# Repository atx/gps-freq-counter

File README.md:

# gps-freq-counter
Frequency counter using a GPS receiver PPS output as its reference

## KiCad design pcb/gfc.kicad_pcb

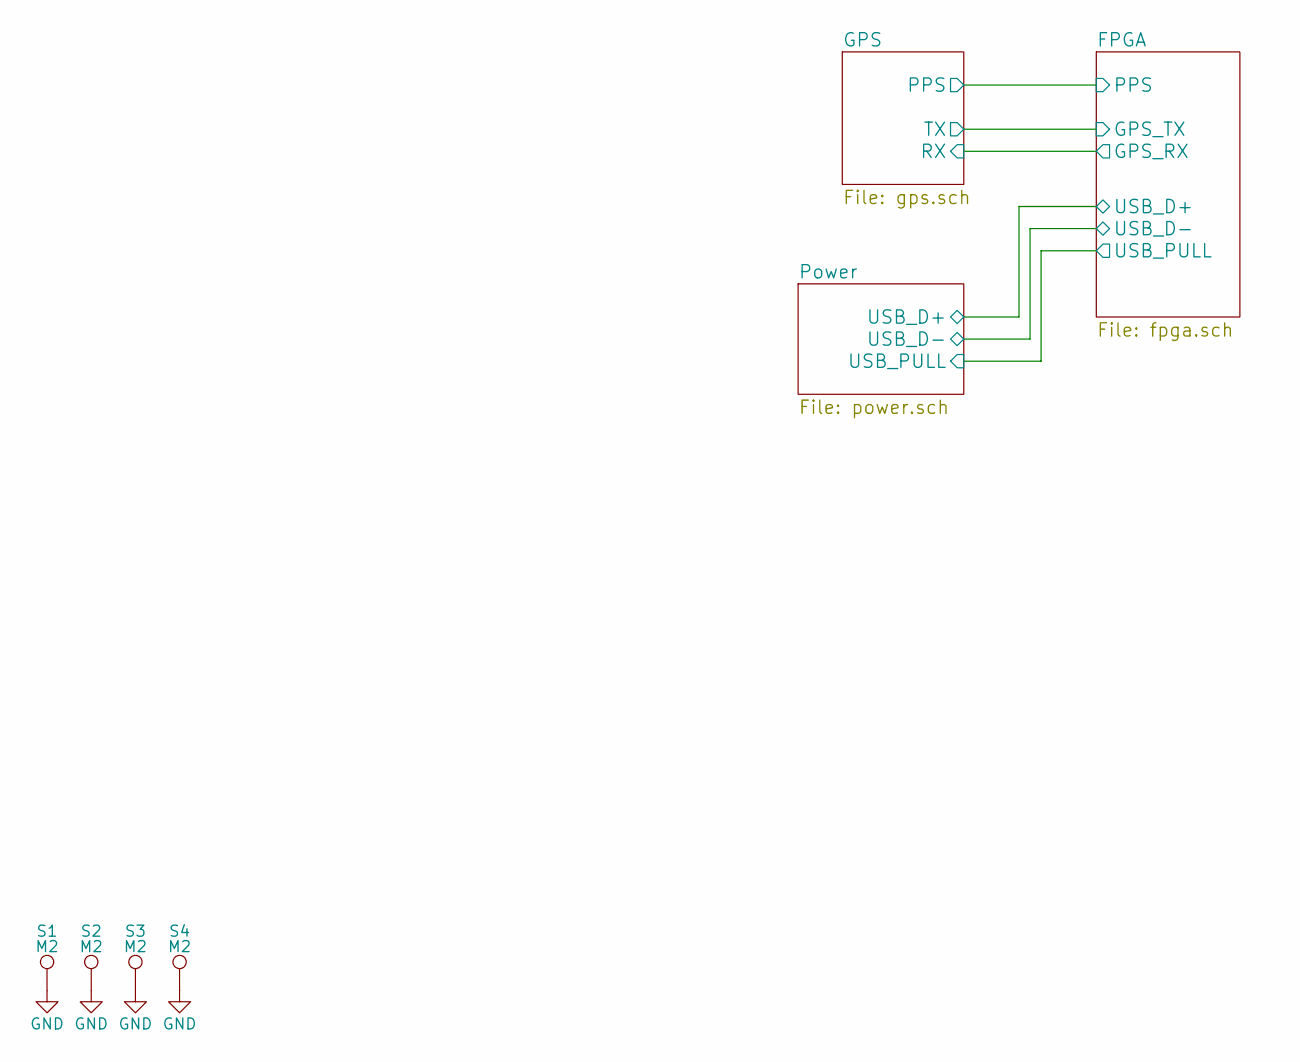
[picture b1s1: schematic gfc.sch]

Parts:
S1, S2, S3, S4: M2; MountingHole_2.2mm_M2_Pad

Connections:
GND: S1.1, S2.1, S3.1, S4.1; also elsewhere on the board

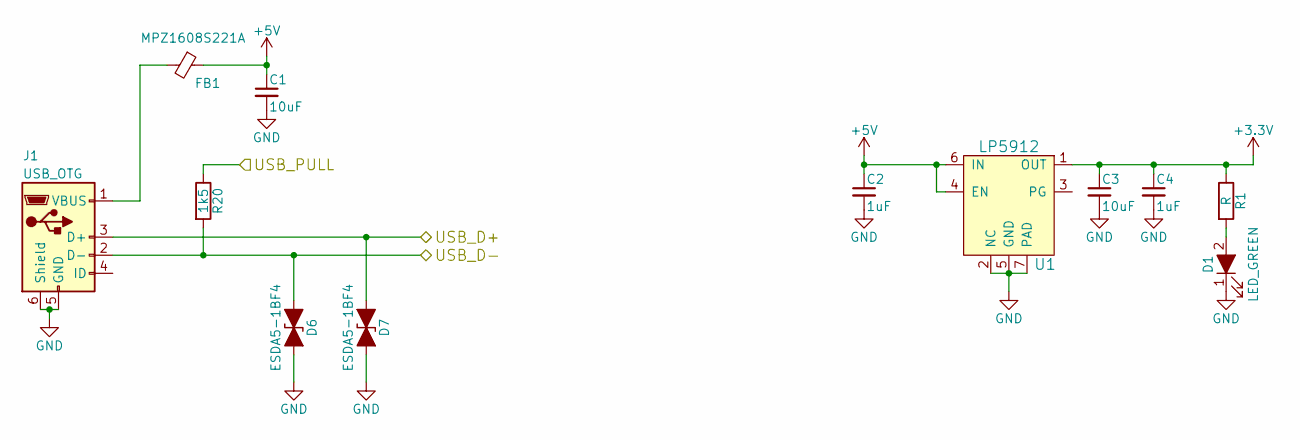
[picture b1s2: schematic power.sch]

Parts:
C1, C3: 10uF; C_0603
C2, C4: 1uF; C_0402
D1: LED_GREEN; LED_0603
D6, D7: ESDA5-1BF4; D_0603
FB1: MPZ1608S221A; L_0603
J1: USB_OTG; USB_Micro-B
R1: R; R_0402
R20: 1k5; R_0402
U1: LP5912; WSON-6-DRV

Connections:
+3V3: C3.1, C4.1, R1.1, U1.1 (OUT); also elsewhere on the board
+5V: C1.1, C2.1, FB1.1, U1.4 (EN), U1.6 (IN)
/FPGA/USB_D+: D7.1 (A1), J1.3 (D+); also elsewhere on the board
/FPGA/USB_D-: D6.1 (A1), J1.2 (D-), R20.2; also elsewhere on the board
/FPGA/USB_PULL: R20.1; also elsewhere on the board
GND: C1.2, C2.2, C3.2, C4.2, D1.1 (K), D6.2 (A2), D7.2 (A2), J1.5 (GND), J1.6 (Shield), U1.2 (NC), U1.5 (GND), U1.7 (PAD); also elsewhere on the board
unnamed: D1.2 (A), R1.2
unnamed: FB1.2, J1.1 (VBUS)

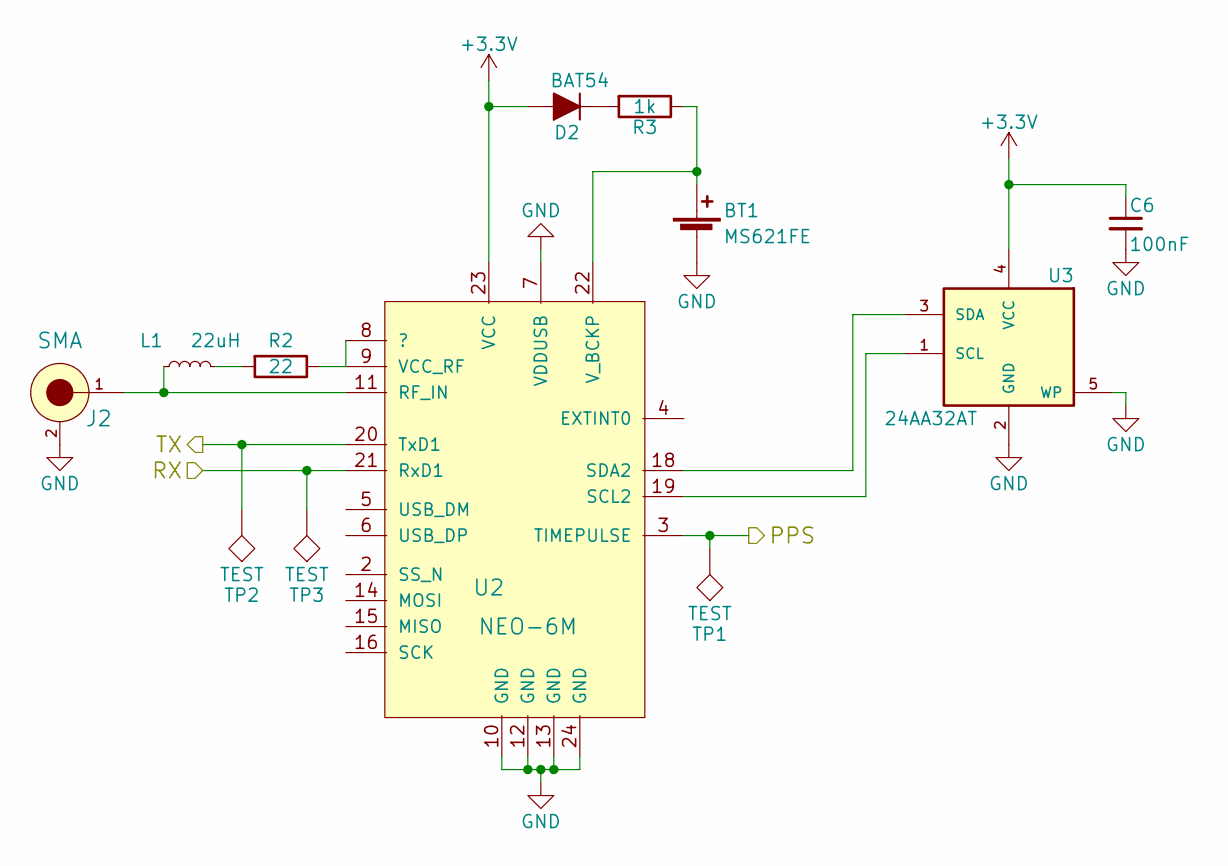
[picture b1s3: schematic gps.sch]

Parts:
BT1: MS621FE
C6: 100nF; C_0402
D2: BAT54; D_SOT-23_ANK
J2: SMA; CON-SMA-EDGE
L1: 22uH; L_0805
R2: 22; R_0402
R3: 1k; R_0402
TP1, TP2, TP3: TEST; PINTST
U2: NEO-6M; NEO-6
U3: 24AA32AT; SOT-23-5

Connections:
+3V3: C6.1, D2.2 (A), U2.23 (VCC), U3.4 (VCC); also elsewhere on the board
/FPGA/GPS_RX: TP3.1, U2.21 (RxD1); also elsewhere on the board
/FPGA/GPS_TX: TP2.1, U2.20 (TxD1); also elsewhere on the board
/FPGA/PPS: TP1.1, U2.3 (TIMEPULSE); also elsewhere on the board
GND: BT1.2 (-), C6.2, J2.2, J2.3, J2.4, J2.5, U2.7 (VDDUSB), U2.10 (GND), U2.12 (GND), U2.13 (GND), U2.24 (GND), U3.2 (GND), U3.5 (WP); also elsewhere on the board
unnamed: BT1.1 (+), R3.1, U2.22 (V_BCKP)
unnamed: D2.1 (K), R3.2
unnamed: J2.1, L1.1, U2.11 (RF_IN)
unnamed: L1.2, R2.2
unnamed: R2.1, U2.8 (?), U2.9 (VCC_RF)
unnamed: U2.18 (SDA2), U3.3 (SDA)
unnamed: U2.19 (SCL2), U3.1 (SCL)

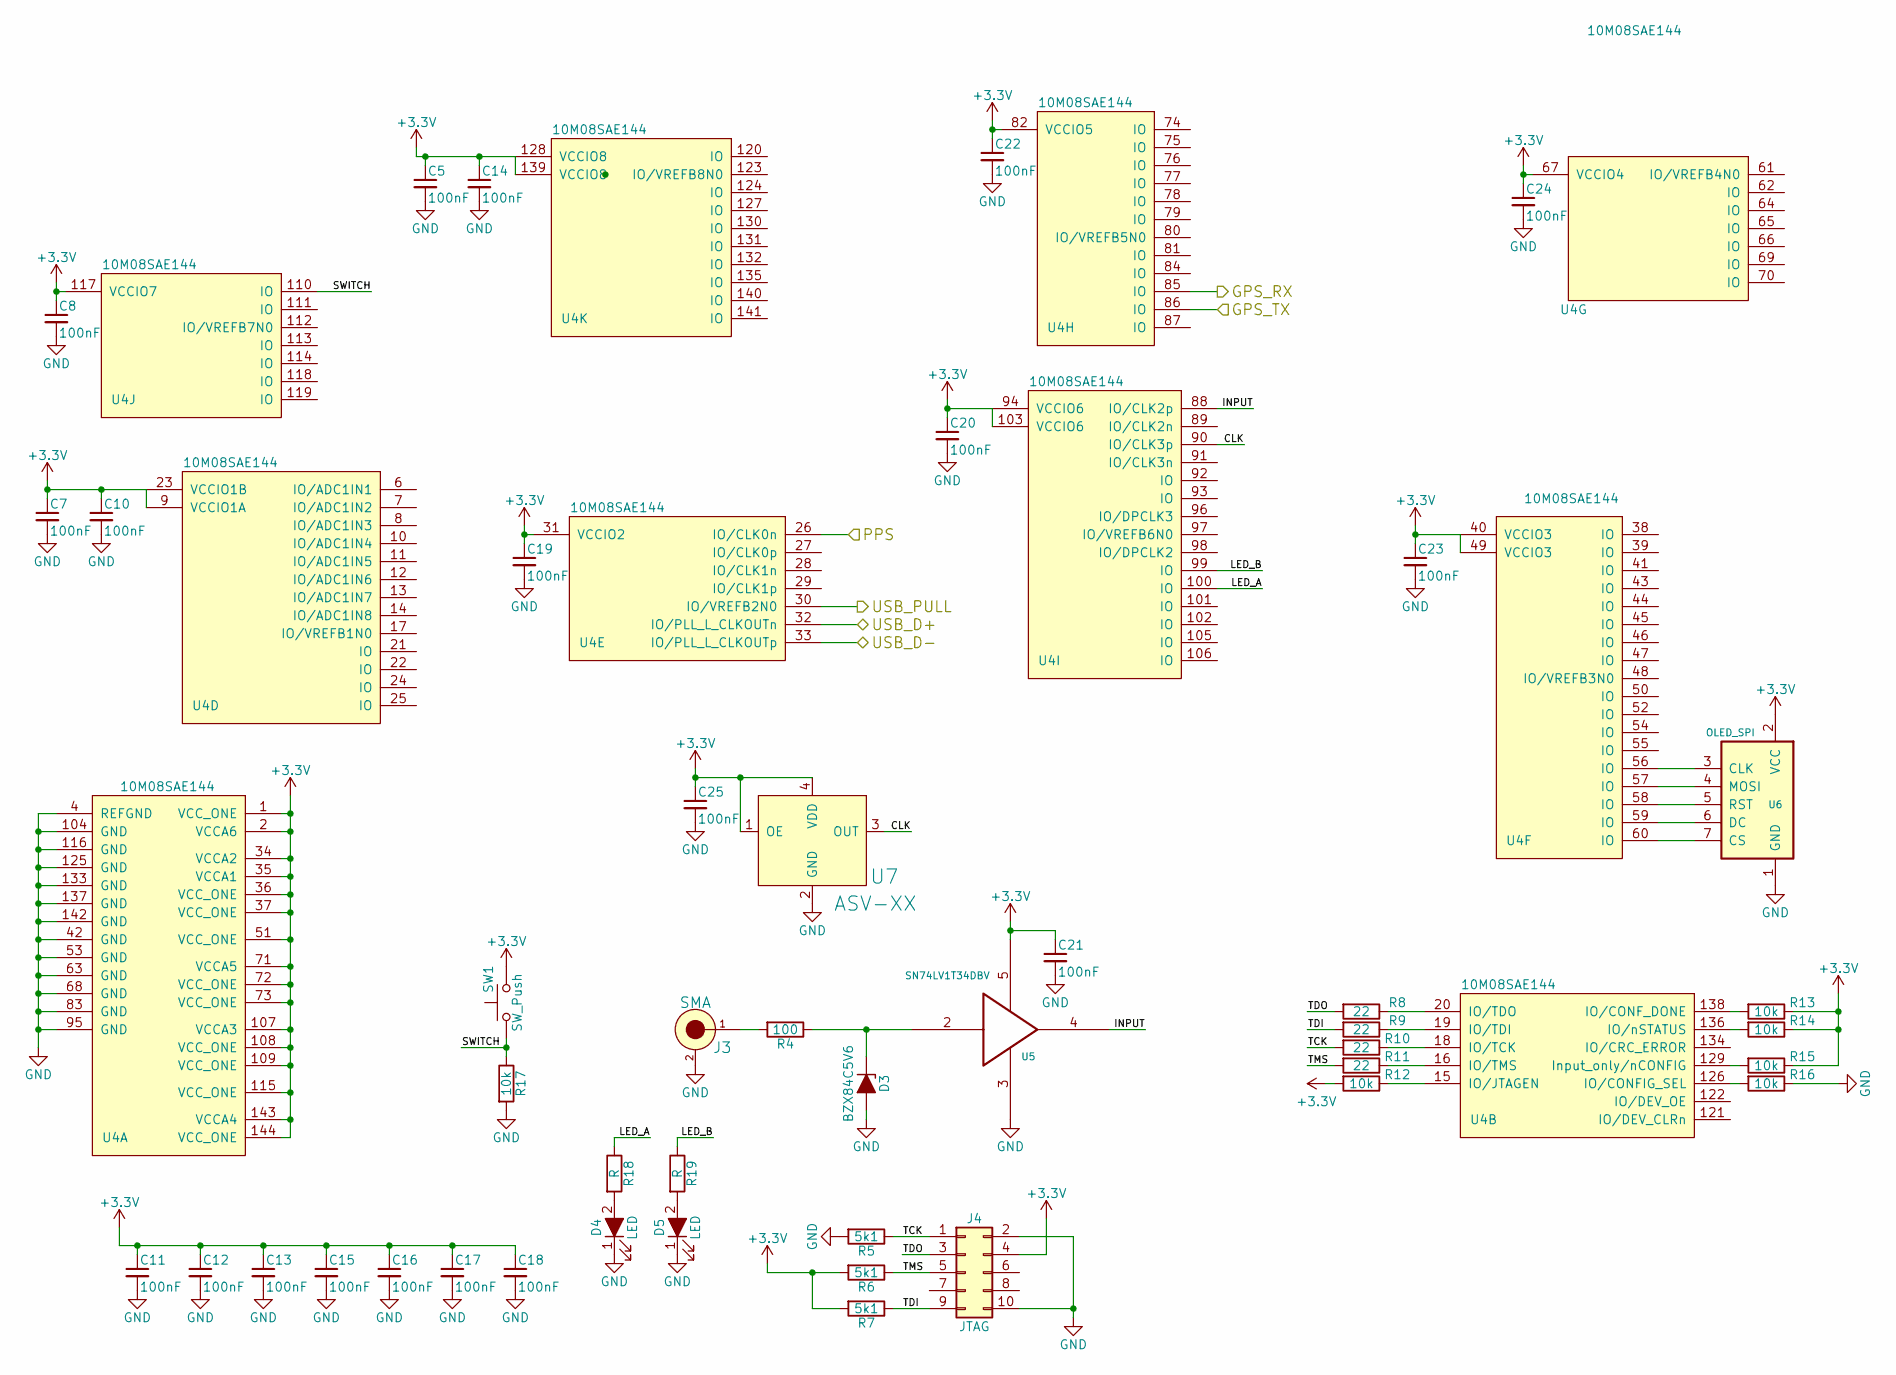
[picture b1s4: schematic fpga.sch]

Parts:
C5, C7, C8, C10, C11, C12, C13, C14, C15, C16, C17, C18, C19, C20, C21, C22, C23, C24, C25: 100nF; C_0402
D3: BZX84C5V6; D_SOT-23_ANK
D4, D5: LED; LED_0603
J3: SMA; CON-SMA-EDGE
J4: JTAG; Pin_Header_Straight_2x05_Pitch2.54mm_SMD
R4: 100; R_0402
R5, R6, R7: 5k1; R_0402
R8, R9, R10, R11: 22; R_0402
R12, R13, R14, R15, R16, R17: 10k; R_0402
R18, R19: R; R_0402
SW1: SW_Push; SW_PUSH_6mm_h13mm
U4: 10M08SAE144; TQFP-144_20x20mm_Pitch0.5mm
U5: SN74LV1T34DBV; SOT-23-5
U6: OLED_SPI
U7: ASV-XX

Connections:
+3V3: C5.1, C7.1, C8.1, C10.1, C11.1, C12.1, C13.1, C14.1, C15.1, C16.1, C17.1, C18.1, C19.1, C20.1, C21.1, C22.1, C23.1, C24.1, C25.1, J4.4, R6.2, R7.2, R12.2, R13.1, R14.1, R15.1, SW1.2, U4.1 (VCC_ONE), U4.2 (VCCA6), U4.9 (VCCIO1A), U4.23 (VCCIO1B), U4.31 (VCCIO2), U4.34 (VCCA2), U4.35 (VCCA1), U4.36 (VCC_ONE), U4.37 (VCC_ONE), U4.40 (VCCIO3), U4.49 (VCCIO3), U4.51 (VCC_ONE), U4.67 (VCCIO4), U4.71 (VCCA5), U4.72 (VCC_ONE), U4.73 (VCC_ONE), U4.82 (VCCIO5), U4.94 (VCCIO6), U4.103 (VCCIO6), U4.107 (VCCA3), U4.108 (VCC_ONE), U4.109 (VCC_ONE), U4.115 (VCC_ONE), U4.117 (VCCIO7), U4.128 (VCCIO8), U4.139 (VCCIO8), U4.143 (VCCA4), U4.144 (VCC_ONE), U5.5, U6.2 (VCC), U7.1 (OE), U7.4 (VDD); also elsewhere on the board
/FPGA/CLK: U4.90 (IO/CLK3p), U7.3 (OUT)
/FPGA/GPS_RX: U4.85 (IO); also elsewhere on the board
/FPGA/GPS_TX: U4.86 (IO); also elsewhere on the board
/FPGA/INPUT: U4.88 (IO/CLK2p), U5.4
/FPGA/LED_A: R18.1, U4.100 (IO)
/FPGA/LED_B: R19.1, U4.99 (IO)
/FPGA/PPS: U4.26 (IO/CLK0n); also elsewhere on the board
/FPGA/SWITCH: R17.1, SW1.1, U4.110 (IO)
/FPGA/TCK: J4.1, R5.1, R10.2
/FPGA/TDI: J4.9, R7.1, R9.2
/FPGA/TDO: J4.3, R8.2
/FPGA/TMS: J4.5, R6.1, R11.2
/FPGA/USB_D+: U4.32 (IO/PLL_L_CLKOUTn); also elsewhere on the board
/FPGA/USB_D-: U4.33 (IO/PLL_L_CLKOUTp); also elsewhere on the board
/FPGA/USB_PULL: U4.30 (IO/VREFB2N0); also elsewhere on the board
GND: C5.2, C7.2, C8.2, C10.2, C11.2, C12.2, C13.2, C14.2, C15.2, C16.2, C17.2, C18.2, C19.2, C20.2, C21.2, C22.2, C23.2, C24.2, C25.2, D3.2 (A), D4.1 (K), D5.1 (K), J3.2, J3.3, J3.4, J3.5, J4.2, J4.10, R5.2, R16.1, R17.2, U4.4 (REFGND), U4.42 (GND), U4.53 (GND), U4.63 (GND), U4.68 (GND), U4.83 (GND), U4.95 (GND), U4.104 (GND), U4.116 (GND), U4.125 (GND), U4.133 (GND), U4.137 (GND), U4.142 (GND), U5.3, U6.1 (GND), U7.2 (GND); also elsewhere on the board
unnamed: D3.1 (K), R4.1, U5.2
unnamed: D4.2 (A), R18.2
unnamed: D5.2 (A), R19.2
unnamed: J3.1, R4.2
unnamed: R8.1, U4.20 (IO/TDO)
unnamed: R9.1, U4.19 (IO/TDI)
unnamed: R10.1, U4.18 (IO/TCK)
unnamed: R11.1, U4.16 (IO/TMS)
unnamed: R12.1, U4.15 (IO/JTAGEN)
unnamed: R13.2, U4.138 (IO/CONF_DONE)
unnamed: R14.2, U4.136 (IO/nSTATUS)
unnamed: R15.2, U4.129 (Input_only/nCONFIG)
unnamed: R16.2, U4.126 (IO/CONFIG_SEL)
unnamed: U4.56 (IO), U6.3 (CLK)
unnamed: U4.57 (IO), U6.4 (MOSI)
unnamed: U4.58 (IO), U6.5 (RST)
unnamed: U4.59 (IO), U6.6 (DC)
unnamed: U4.60 (IO), U6.7 (CS)

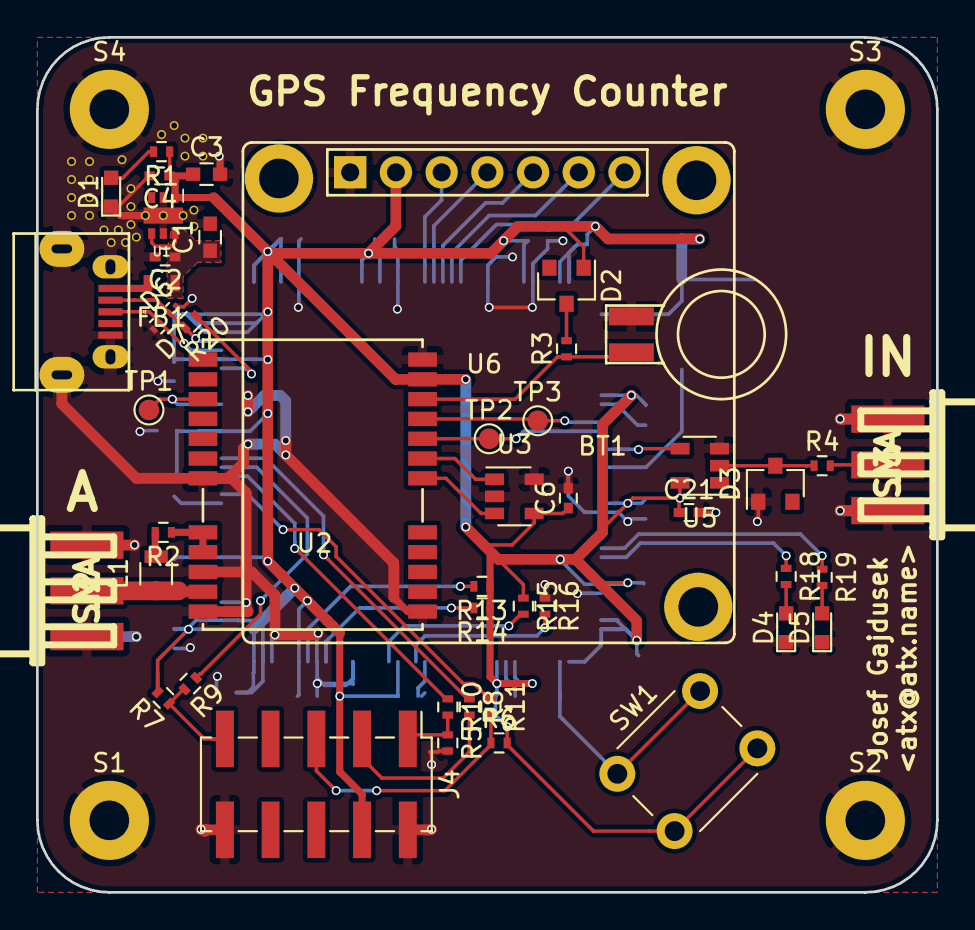
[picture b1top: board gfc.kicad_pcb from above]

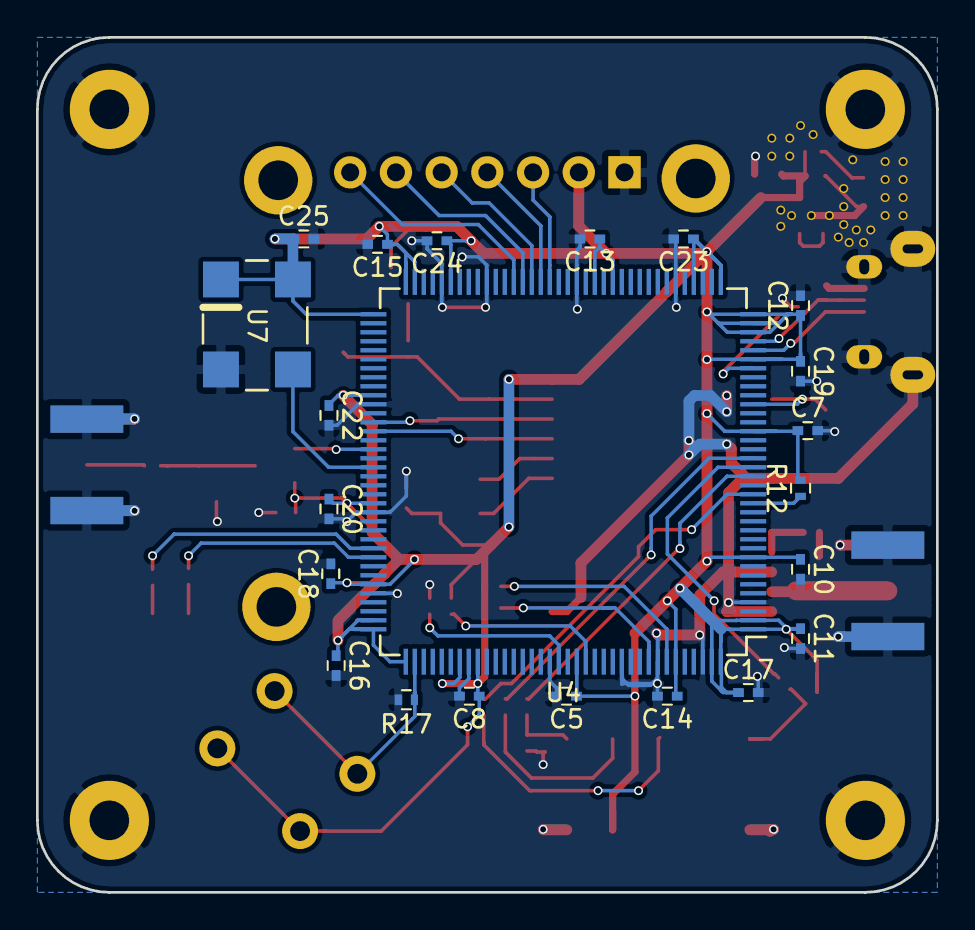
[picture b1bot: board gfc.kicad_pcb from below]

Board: 2 copper layers, 50.0 x 47.5 mm, 73 parts (22 on the bottom side), 45 nets.

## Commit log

2018-02-24 Initial FPGA commit
    Create new Chisel project with some code
2018-03-02 fpga: Add the vcd_autolink.fish script
    Chisel really likes to randomly create new test output directories every once
    in a while. This is a hacky way of not having to restart gtkwave
2018-03-02 fpga: Add Memory and ReadOnlyMemory
2018-03-02 pcb: Add the PCB
2018-03-02 fpga: Add rudimentary PicoRV32 test
    Just to make sure it is actually doing something --- the repo contains much
    more comprehensive test suite
2018-03-04 fpga: MemoryMux: Pass the ready flag back to the master
    Welp...
2018-03-04 fpga: PicoRV: Add a more comprehensive test
2018-03-05 fpga: Memory: Factor out memory connecting code
2018-03-09 fpga: Add SPI module
2018-03-09 fpga: Bump Scala version
2018-03-09 fpga: Memory: Fix the ready signal being asserted too soon
    I seriously suck at this...
2018-03-09 fpga/src: Add a more complicated PicoRV test
2018-03-09 fpga: BusTester: Add forgotten file
    Oops...
2018-03-11 fpga: MemoryMux improve constructor argument structure
2018-03-23 fpga: Improve SPI tests
2018-03-23 src: Enable compiler warnings
2018-03-23 fpga: PicoRVTests: Don't break when oddly sized firmware file
2018-03-23 src: Handle .bss/.data sections properly
2018-03-23 fpga/src: Add SPI integration test
2018-03-23 fpga: PicoRVTests: Abstract some shared code
2018-03-24 fpga: BusTester: Initialize the bus to zeros on test start
2018-03-24 fpga: BusTester: Add support for read timeout
2018-03-24 fpga: Add UART transceiver implementation
2018-03-24 fpga: MemoryMux: Add convenience build function
2018-03-24 fpga: ReadOnlyMemory: Add convenience function for loading from a resouce file
2018-03-24 fpga: VerilogInitializedMemory: Add
    Add a BlackBox verilog module, which allows for painless memory preloading.
    For some reason, just loading the data to a Vec leads to fairly weird Verilog,
    which in turn does not properly get inferred by Quartus as preload-RAM
2018-03-24 fpga: VerilogInitializedMemory: Handle memory size properly
2018-03-24 fpga: Add PPSCounter module
2018-03-29 fpga: bsdl: Add BSDL file
2018-03-29 src: Build verilog memh files
2018-03-29 fpga: Group SPI signals in SPIBundle
2018-03-29 src: Generate the memh files from the correct source
2018-03-29 fpga: PicoRVTests: Switch to the Verilog-based memory implementation
2018-03-29 fpga: SPI: Tie the CS pin to the SPI peripheral
2018-03-30 First real working-on-hardware build
2018-03-31 fpga: Fix the PLL
    Turns out that 100nF for each pin group isn't really sufficient decoupling
2018-03-31 fpga: MemoryMux: Switch to Mux1H
    This is unsurprisingly much faster and smaller
2018-04-01 fpga: Add millisecond timer register
2018-04-01 fpga: PicoRVTests: Disable the main program tests
    Takes way too long for my liking and does not "test" anything anyway
2018-04-01 src: cmake: Run size after building the binary
2018-04-01 fpga: AcknowledgeRegister: Add
2018-04-01 fpga: Debouncer: Add
2018-04-01 fpga: tests: DRY while starting test runners
2018-04-01 fpga: AcknowledgeRegister.build: Fix stupid bug
2018-04-01 Initial UI stuff
2018-04-01 fpga: tests: GFCSpec: Actually commit the file...
2018-04-01 fpga: SPI: Allow only single ported reads
2018-04-01 src: sprites/status_key_*: Make the icon a bit rounder
2018-04-01 fpga: SPI: Fix write not being performed in some circumstances
2018-04-01 fpga: UART: Externalize the status flags
2018-04-01 src: Initial support for the GPS module
2018-04-05 src: Render '?' when we haven't received a GPS status message for a long time
2018-04-06 src: oled: Somewhat better bit blitting
2018-04-06 src: Verify the NMEA message checksums
2018-04-08 mech: First version of the enclosure
    To be printed
2018-04-12 fpga: quartus: Finally commit the quartus project
2018-04-12 fpga: Switch to using MIF files for the Quartus toolchain
    Faster firmware reloading this way
2018-04-12 fpga: UARTTests: Minor improvement
2018-04-12 fpga: Allow specifying larger-than-actual size for MIF file initialization
    Quartus was fucking the MIF-only update up after the size has grown
2018-04-12 Switch to the UBX binary protocol for the GPS module
2018-04-12 src: gps: Count all channels where signal is acquired
2018-04-12 src: Show the measurement value
2018-04-28 src: Nicer measurement value rendering
2018-04-28 mech: Box update
2018-04-28 ui: Add support for longer integration times
2018-04-28 src: Optimize oled_fill
2018-04-28 src: Clear the space where measurement value will be rendered
2018-04-28 src: Don't render stuff unless it was updated
2018-04-28 src: Flip submenu button order
2018-04-28 ui: sprites: status_pps_*: Commit forgotten files
2018-04-28 ui: main: Commit the ui_on_pps call...
    I should really be paying better attention...
2018-04-28 ui: main: Signal activity with LED A
2018-04-28 src: ui: Render decimal separator
2018-04-28 Add support for input selection
2018-04-30 src: ui: Nicer progress bar
2018-05-03 src: Signal ublox state activity with the second LED
2018-05-03 src: Switch to a time-specific type
2018-05-03 src: Show difference from a guessed "ideal" oscillator frequency
2018-05-05 src: Wait for the ublox module to properly initialize bevore sending the config messages
2018-05-05 schema: Add a block schematic
2018-05-05 schema: Fix missing lines
2018-06-30 src: bintoverilog: Handle correctly odd-sized files
2018-06-30 Add crude USB implementation
    Still needs a ton of work, but it does something.
2018-06-30 src: usb: Fix wTotalLength in the configuration descriptor
    Oops, lsusb really dislikes that zero
2018-07-01 src: usb: Add an interface descriptor
2018-07-01 fpga: USB: Clear output buffer on receiving a SETUP packet
    This prevents sending wrong data on receiving a new SETUP packet.
    (maybe this should be expanded even more?)
2018-07-01 src: Add command to fetch current measurement data
2018-07-01 Major USB stability improvements
2018-07-01 fpga: usb: Synchronizer: Add single cycle output delay
    Helps with timing closure
2018-07-06 src: main: Prettier handler dispatch code
2018-07-06 src: Add USB OLED status symbol
    Also includes some restructuring which I was too lazy to factor out.
2018-07-06 Drop the RV -E suffix
    Does not seem to help anything anyway and the toolchain is a headache.
2018-07-06 Bunch of stuff...
2018-07-06 src: usb: Move command handlers to a struct-table
2018-07-06 src: Fix ui_on_pps getting called without the argument
2018-07-06 fpga: Move USB-stuff construction to a separate Module
2018-07-06 src: usb: Add command to fetch GPS status
2018-07-06 fpga: quartus: Add flashonly subcommand
2018-07-06 src: usb: Add input selection command
2018-07-13 py: More user-friendly measurement mode
2018-07-13 fpga: tests: Switch from BusTester to BusHelper
2018-07-13 pcb: Add a lingering file
    Looks like eeschema -> pcbnew file (?)
2018-07-13 fpga: Move ReadOnlyMemory
    Seeing as its used only in the test anyway...
2018-07-13 fpga: usb: Minor code cleanups
2018-07-13 usb: Calculate the TX CRC16 in hardware
2018-07-15 Remove a bunch of irrelevant TODOs
2018-07-15 src: Cleaner state separation
2018-07-15 src: ublox: Add forgotten timestamp update
2018-07-15 Measure both channels simultaneously
2018-07-15 src: ui: Drop the unused render_status function
2018-07-15 src: ui: Drop the ui_init function
    Does nothing anyway...
2018-07-15 src: main: Don't blink the LED for status handlers
    These are getting called all the time, which made the LED useless as
    an indicator of activity.
2018-07-21 schema: Add the USB connection
